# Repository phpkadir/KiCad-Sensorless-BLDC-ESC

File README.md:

# KiCad-Sensorless-BLDC-ESC

I designed this pcb because I want to be able to try different microcontrollers as part of Electronic Speed Controller projects. It can be used with especially the microcontrollers those don't have the internal comparator capability.

I ordered the version 0.3 and will test it when it arrives.

I made some mistakes about connections of the mosfet circuits. I will fix those mistakes in the next update.

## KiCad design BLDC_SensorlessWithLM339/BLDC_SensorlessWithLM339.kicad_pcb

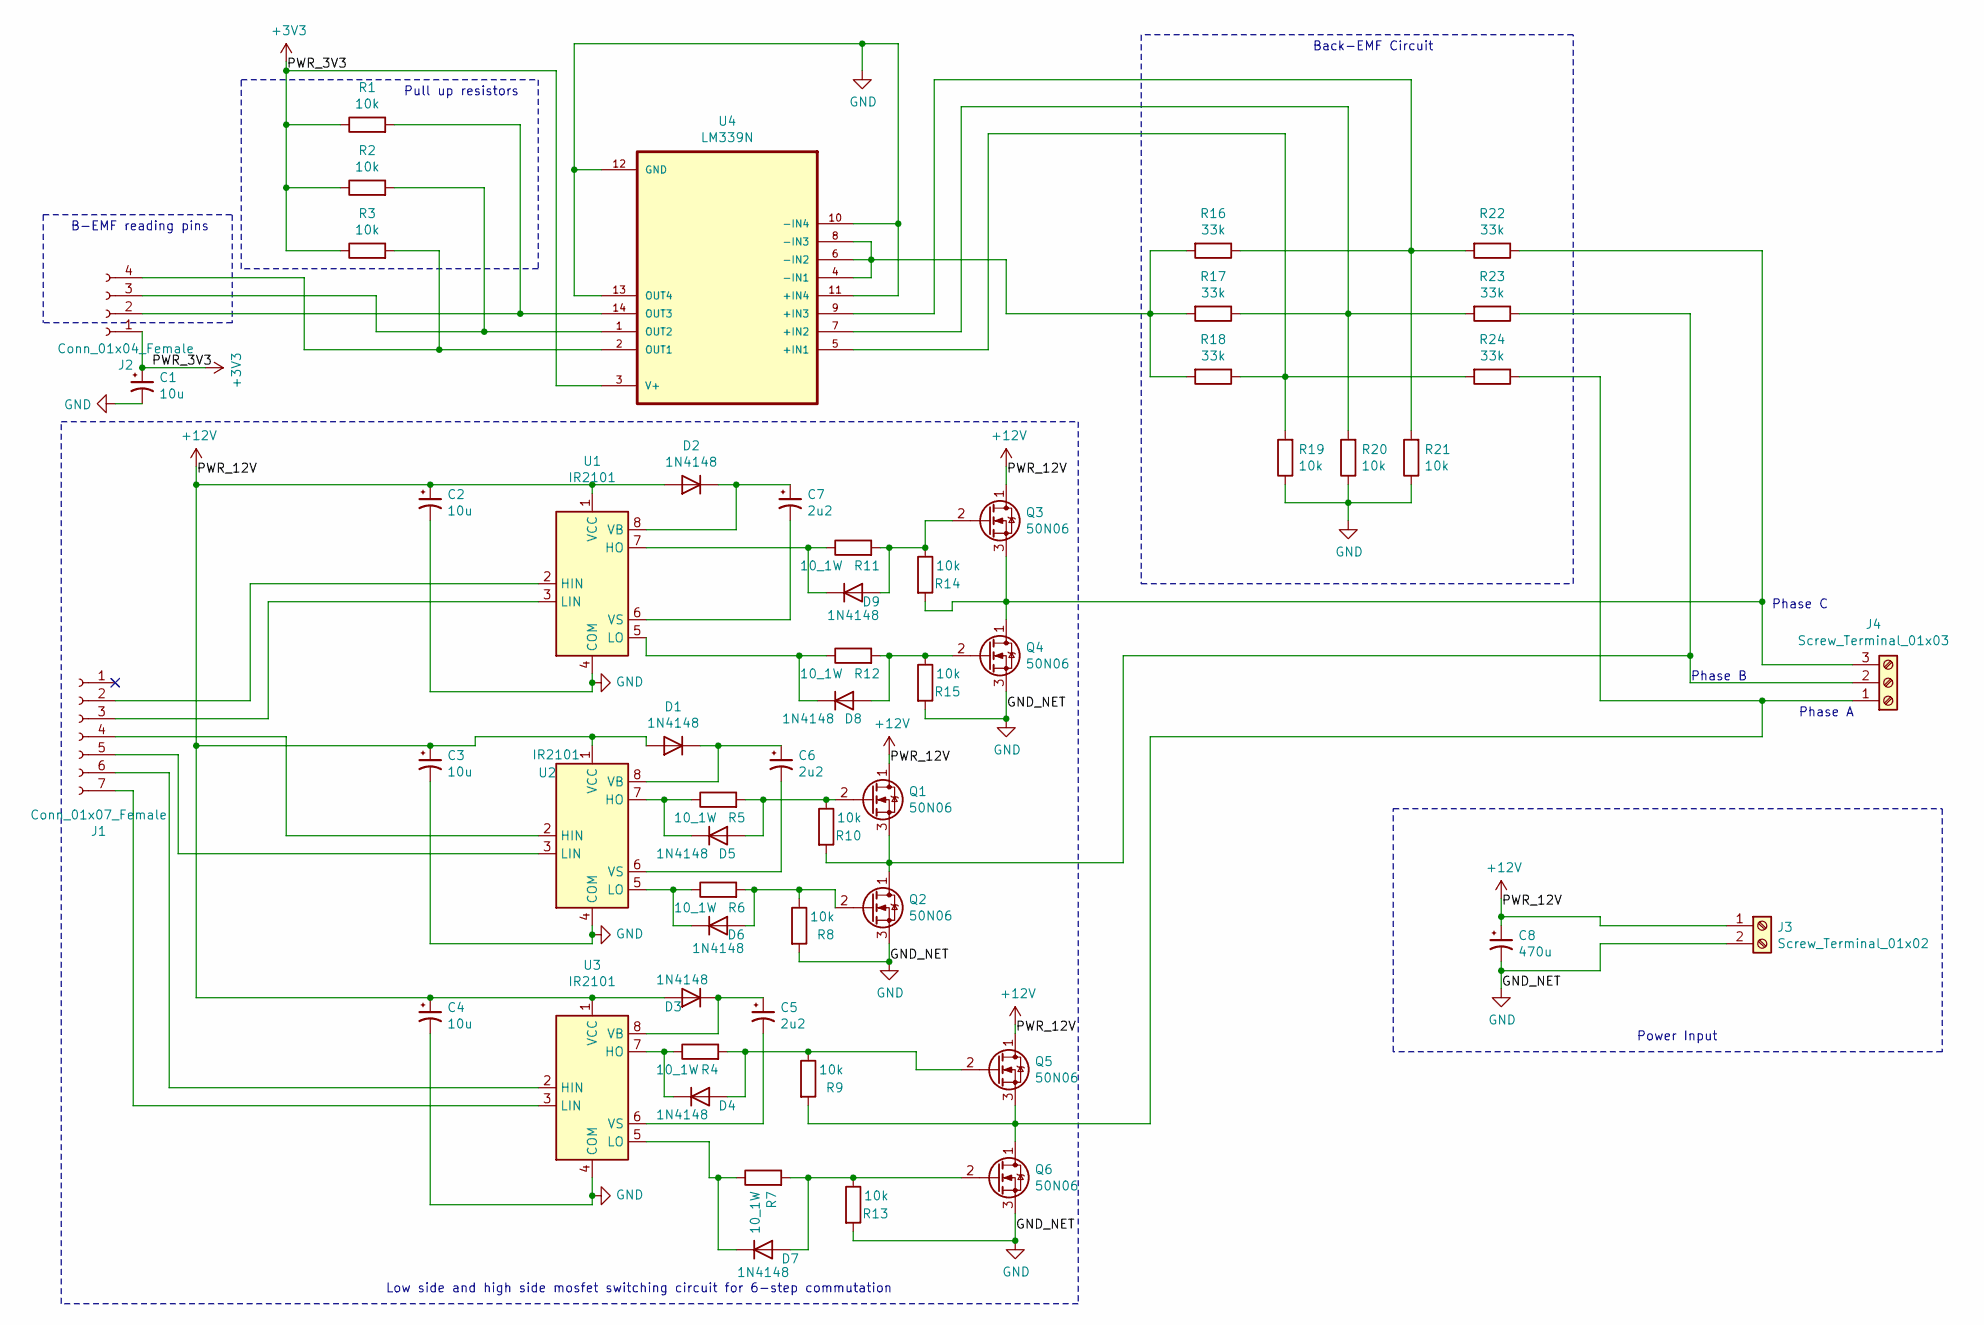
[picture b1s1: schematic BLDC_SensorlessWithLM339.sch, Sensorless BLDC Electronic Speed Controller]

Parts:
C1, C2, C3, C4: 10u; CP_Radial_D5.0mm_P2.50mm
C5, C6, C7: 2u2; CP_Radial_D5.0mm_P2.50mm
C8: 470u; CP_Radial_D10.0mm_P5.00mm
D1, D2, D3, D4, D5, D6, D7, D8, D9: 1N4148; D_DO-35_SOD27_P7.62mm_Horizontal
J1: Conn_01x07_Female; PinSocket_1x07_P2.54mm_Vertical
J2: Conn_01x04_Female; PinSocket_1x04_P2.54mm_Vertical
J3: Screw_Terminal_01x02; TerminalBlock_bornier-2_P5.08mm
J4: Screw_Terminal_01x03; TerminalBlock_bornier-3_P5.08mm
Q1, Q2, Q3, Q4, Q5, Q6: 50N06; TO-220-3_Vertical
R1, R2, R3, R8, R9, R10, R13, R14, R15, R19, R20, R21: 10k; R_0805_2012Metric_Pad1.20x1.40mm_HandSolder
R4, R5, R6, R7, R11, R12: 10_1W; R_2512_6332Metric_Pad1.40x3.35mm_HandSolder
R16, R17, R18, R22, R23, R24: 33k; R_0805_2012Metric_Pad1.20x1.40mm_HandSolder
U1, U2, U3: IR2101; DIP-8_W7.62mm_LongPads
U4: LM339N; DIP794W45P254L1969H508Q14

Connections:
+3V3: C1.1, J2.1, R1.1, R2.1, R3.1, U4.3 (V+)
+12V: C2.1, C3.1, C4.1, C8.1, D1.2 (A), D2.2 (A), D3.2 (A), J3.1, Q1.1 (D), Q3.1 (D), Q5.1 (D), U1.1 (VCC), U2.1 (VCC), U3.1 (VCC)
GND: C1.2, C2.2, C3.2, C4.2, C8.2, J3.2, Q2.3 (S), Q4.3 (S), Q6.3 (S), R8.2, R13.2, R15.2, R19.1, R20.1, R21.1, U1.4 (COM), U2.4 (COM), U3.4 (COM), U4.10 (-IN4), U4.11 (+IN4), U4.12 (GND), U4.13 (OUT4)
unnamed: C5.1, D3.1 (K), U3.8 (VB)
unnamed: C5.2, U3.6 (VS)
unnamed: C6.1, D1.1 (K), U2.8 (VB)
unnamed: C6.2, U2.6 (VS)
unnamed: C7.1, D2.1 (K), U1.8 (VB)
unnamed: C7.2, U1.6 (VS)
unnamed: D4.1 (K), R4.1, U3.7 (HO)
unnamed: D4.2 (A), Q5.2 (G), R4.2, R9.1
unnamed: D5.1 (K), R5.1, U2.7 (HO)
unnamed: D5.2 (A), Q1.2 (G), R5.2, R10.1
unnamed: D6.1 (K), R6.1, U2.5 (LO)
unnamed: D6.2 (A), Q2.2 (G), R6.2, R8.1
unnamed: D7.1 (K), R7.1, U3.5 (LO)
unnamed: D7.2 (A), Q6.2 (G), R7.2, R13.1
unnamed: D8.1 (K), R12.1, U1.5 (LO)
unnamed: D8.2 (A), Q4.2 (G), R12.2, R15.1
unnamed: D9.1 (K), R11.1, U1.7 (HO)
unnamed: D9.2 (A), Q3.2 (G), R11.2, R14.1
unnamed: J1.2, U1.2 (HIN)
unnamed: J1.3, U1.3 (LIN)
unnamed: J1.4, U2.2 (HIN)
unnamed: J1.5, U2.3 (LIN)
unnamed: J1.6, U3.2 (HIN)
unnamed: J1.7, U3.3 (LIN)
unnamed: J2.2, R1.2, U4.14 (OUT3)
unnamed: J2.3, R2.2, U4.1 (OUT2)
unnamed: J2.4, R3.2, U4.2 (OUT1)
unnamed: J4.1, Q5.3 (S), Q6.1 (D), R9.2, R24.1
unnamed: J4.2, Q1.3 (S), Q2.1 (D), R10.2, R23.1
unnamed: J4.3, Q3.3 (S), Q4.1 (D), R14.2, R22.1
unnamed: R16.1, R21.2, R22.2, U4.9 (+IN3)
unnamed: R16.2, R17.2, R18.2, U4.4 (-IN1), U4.6 (-IN2), U4.8 (-IN3)
unnamed: R17.1, R20.2, R23.2, U4.7 (+IN2)
unnamed: R18.1, R19.2, R24.2, U4.5 (+IN1)

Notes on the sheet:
Low side and high side mosfet switching circuit for 6-step commutation
Back-EMF Circuit
Phase A
Phase B
Phase C
Power Input
Pull up resistors
B-EMF reading pins

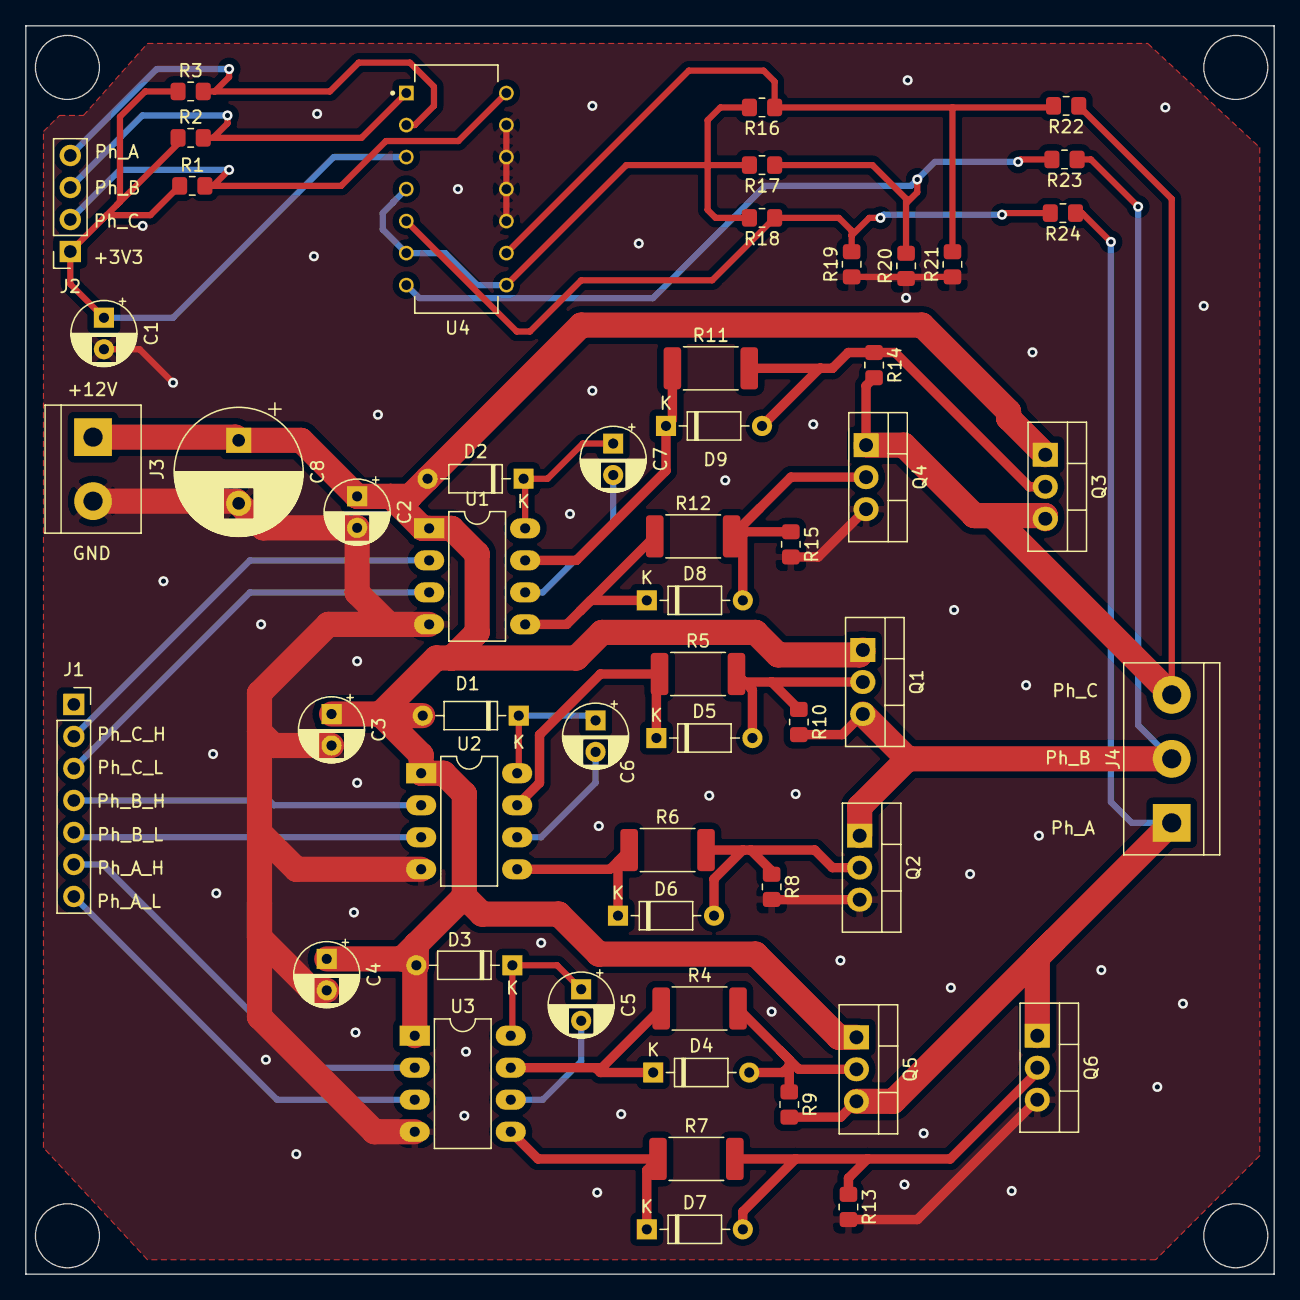
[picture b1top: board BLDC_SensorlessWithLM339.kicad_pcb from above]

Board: 2 copper layers, 99.1 x 99.1 mm, 55 parts (0 on the bottom side), 37 nets.

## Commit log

2020-12-10 Versin 0.1
    Version 0.1
2020-12-14 Updated to Version 0.2
    Updated to version 0.2. Now pcb holds only 10x10 cm^2 field.
2020-12-14 Updated to version 0.2
    PCB holds only 10x10 cm^2 field now. I need to test it.
2020-12-19 Version 0.3
    I ordered the PCB. I will test it when it arrives.
